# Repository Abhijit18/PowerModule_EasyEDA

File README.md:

# XIAO ESP32-C3 / 18650 Mini-UPS — Copilot + EasyEDA Pro Engineering Workspace

> **ENGINEERING DEVELOPMENT / NO FABRICATION APPROVAL.** This is a complete Git repository of requirements, source design artifacts, engineering evidence, scripts, firmware test harness, and AI assistant instructions. It is **not** a finished or verified Rev C PCB. The original Gerber package and Rev B PCB are evidence / draft baselines, not certified source of truth for electrical equivalence.

## Mission
Rework the supplied power-switching board into an affordable, hand-assemblable EasyEDA Pro design. A single *protected 18650 3.7 V nominal* cell and the existing XIAO ESP32-C3 onboard USB charger/power circuitry should keep a **verified-compatible 3.3 V microphone** and ESP32 alive through 5 V input failures, while a **D1/GPIO3-driven transistor** controls a relay. Preserve D2–D10 GPIO breakouts and relay NO/COM/NC; document any original-function differences. Prefer through-hole carrier components; the preassembled XIAO is necessarily SMT internally.

## What is included

| Folder / file | Purpose |
|---|---|
| `reference/original/` | User's original schematic PNG and Gerber ZIP; immutable historical input |
| `reference/rev-b/` | Rev B EasyEDA Standard JSON, KiCad draft, native previews and supplier BOM, **unvalidated** |
| `hardware/rev-c/` | Revision C target design contract, net map, component target, holder fit checks |
| `docs/` | Electrical architecture, source traceability, decisions, BOM, risks, validation and fabrication gates |
| `.github/copilot-instructions.md` / `AGENTS.md` | Always-on AI guardrails and navigation |
| `.github/agents/` | Specialist electrical, EasyEDA, reviewer, sourcing and test agents |
| `.github/skills/` | Reusable MCP, power-path, schematic, PCB, BOM and bring-up playbooks |
| `.github/prompts/` | Ready-to-run Copilot slash prompts by engineering phase |
| `.vscode/mcp.json` | Project-local MCP server with **read-only** starting profile |
| `firmware/` | Non-production heartbeat/relay verification sketch |
| `scripts/` and `tests/` | Executable requirements and file integrity checks |
| `evidence/` | Templates for per-revision engineering review evidence |

## Getting started (Windows / VS Code / EasyEDA Pro)

1. Extract this repository, open its **root folder** in VS Code, and enable GitHub Copilot Chat.
2. Install **Node.js 24.x** and EasyEDA Pro. Read [`docs/mcp-setup.md`](docs/mcp-setup.md). The `npx` MCP install needs internet access and the EasyEDA extension must be imported in the Pro UI.
3. Run `npx easyeda-mcp-pro extension --open`; import `easyeda-bridge-extension.eext` in **Advanced → Extensions Manager**, allow external interaction, restart EasyEDA Pro, and use **MCP Bridge → Connect Local**.
4. In VS Code start the `easyeda-mcp-pro` MCP server using `.vscode/mcp.json`; open a disposable EasyEDA Pro project or import the Rev B Standard JSON as an **unverified baseline**. Run `npx easyeda-mcp-pro --doctor` if offline.
5. In Copilot Chat choose **circuit-architect** agent and run `/audit-original-circuit`, then `/design-rev-c-schematic` with existing project focused in EasyEDA Pro.
6. Only after reviewing the proposed changes, switch MCP to a suitable **write-capable tool profile** and grant explicit, scoped approval for changes (`confirmWrite=true` where required). **Do not enable unsupervised writes or generate manufacturing files as the first action.**
7. Run `python scripts/validate_repo.py` and `python -m unittest discover -s tests -v` locally. CI checks reference integrity, documented requirements and evidence file references, **not** electrical functionality. Executed tests and PASS gates require actual evidence paths rather than blanket NOT_RUN status.

### First Copilot request

> Read `AGENTS.md`, `docs/requirements.md`, `docs/architecture.md`, `docs/source-traceability.md`, and `hardware/rev-c/design-contract.json`. First call EasyEDA MCP read-only tools to inspect the focused project (list components, nets, XIAO pin map, battery/relay connections, project identity). Produce a pin-by-pin discrepancy matrix vs the original schematic and Rev B draft, distinguishing verified facts from assumptions. Do not write to EasyEDA or change the 5 V power circuitry yet. Propose a Rev C schematic plan and missing evidence.

## Engineering status

- **Original**: Schematic and Gerbers supplied by owner; original board may have external 5 V boost, charge-status and power-switch semantics that Rev B changed.
- **Rev B**: Files imported as draft reference; not independently opened in EasyEDA Pro or checked with its ERC/DRC. Its original design docs explicitly flag several non-equivalent interfaces.
- **Rev C**: Target requirements and process packaged here. **No native EasyEDA Pro Rev C schematic, routed PCB, tested 18650 footprint or Gerbers are claimed**.
- **Hard release blockers**: microphone nominal voltage/current unknown; exact 18650 cell/holder dimensions unknown; state of charger and external-5V path not verified on actual XIAO revision; combined 3.3 V peak current not measured; source-to-target functional equivalence incomplete.

### Push to GitHub (after extracting)

This ZIP contains a local Git repository with an initial commit. No GitHub remote is automatically created.

```powershell
# In a PowerShell terminal inside the extracted folder:
git status
# Create a new *private* repository on GitHub using the web UI, then:
git remote add origin https://github.com/YOUR-USER/xiao-esp32c3-ups-copilot.git
git push -u origin main
```

If `gh` is installed and authenticated, an alternative is `gh repo create xiao-esp32c3-ups-copilot --private --source . --remote origin --push`. Review all reference files before publishing; the original design is included.

## Essential boundaries

Never connect 230 V AC directly to the 5 V terminal. Never put an unprotected lithium cell into a charger circuit without verifying its safety requirements. Never infer a manufacturing-safe PCB from a pretty 3D concept or autorouter's zero-unconnected result. Keep the original and Rev B references read-only and do all edits under `hardware/rev-c/` / an explicitly named EasyEDA Pro project. See `docs/safety-gates.md`.

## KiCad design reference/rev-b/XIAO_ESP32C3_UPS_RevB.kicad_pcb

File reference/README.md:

# Immutable source evidence

`original/` is the owner's uploaded schematic and Gerber ZIP. `rev-b/` are assistant-produced draft EasyEDA Standard and KiCad artifacts **not independently verified inside EasyEDA Pro**. These are historical references, not engineering release files; do not alter their contents. New editable designs belong in `hardware/rev-c/` and in a separate owner-approved EasyEDA Pro project. Source files can contain errors and require datasheet + native net/readback validation. These files may be proprietary; review sharing before pushing to a public repository.

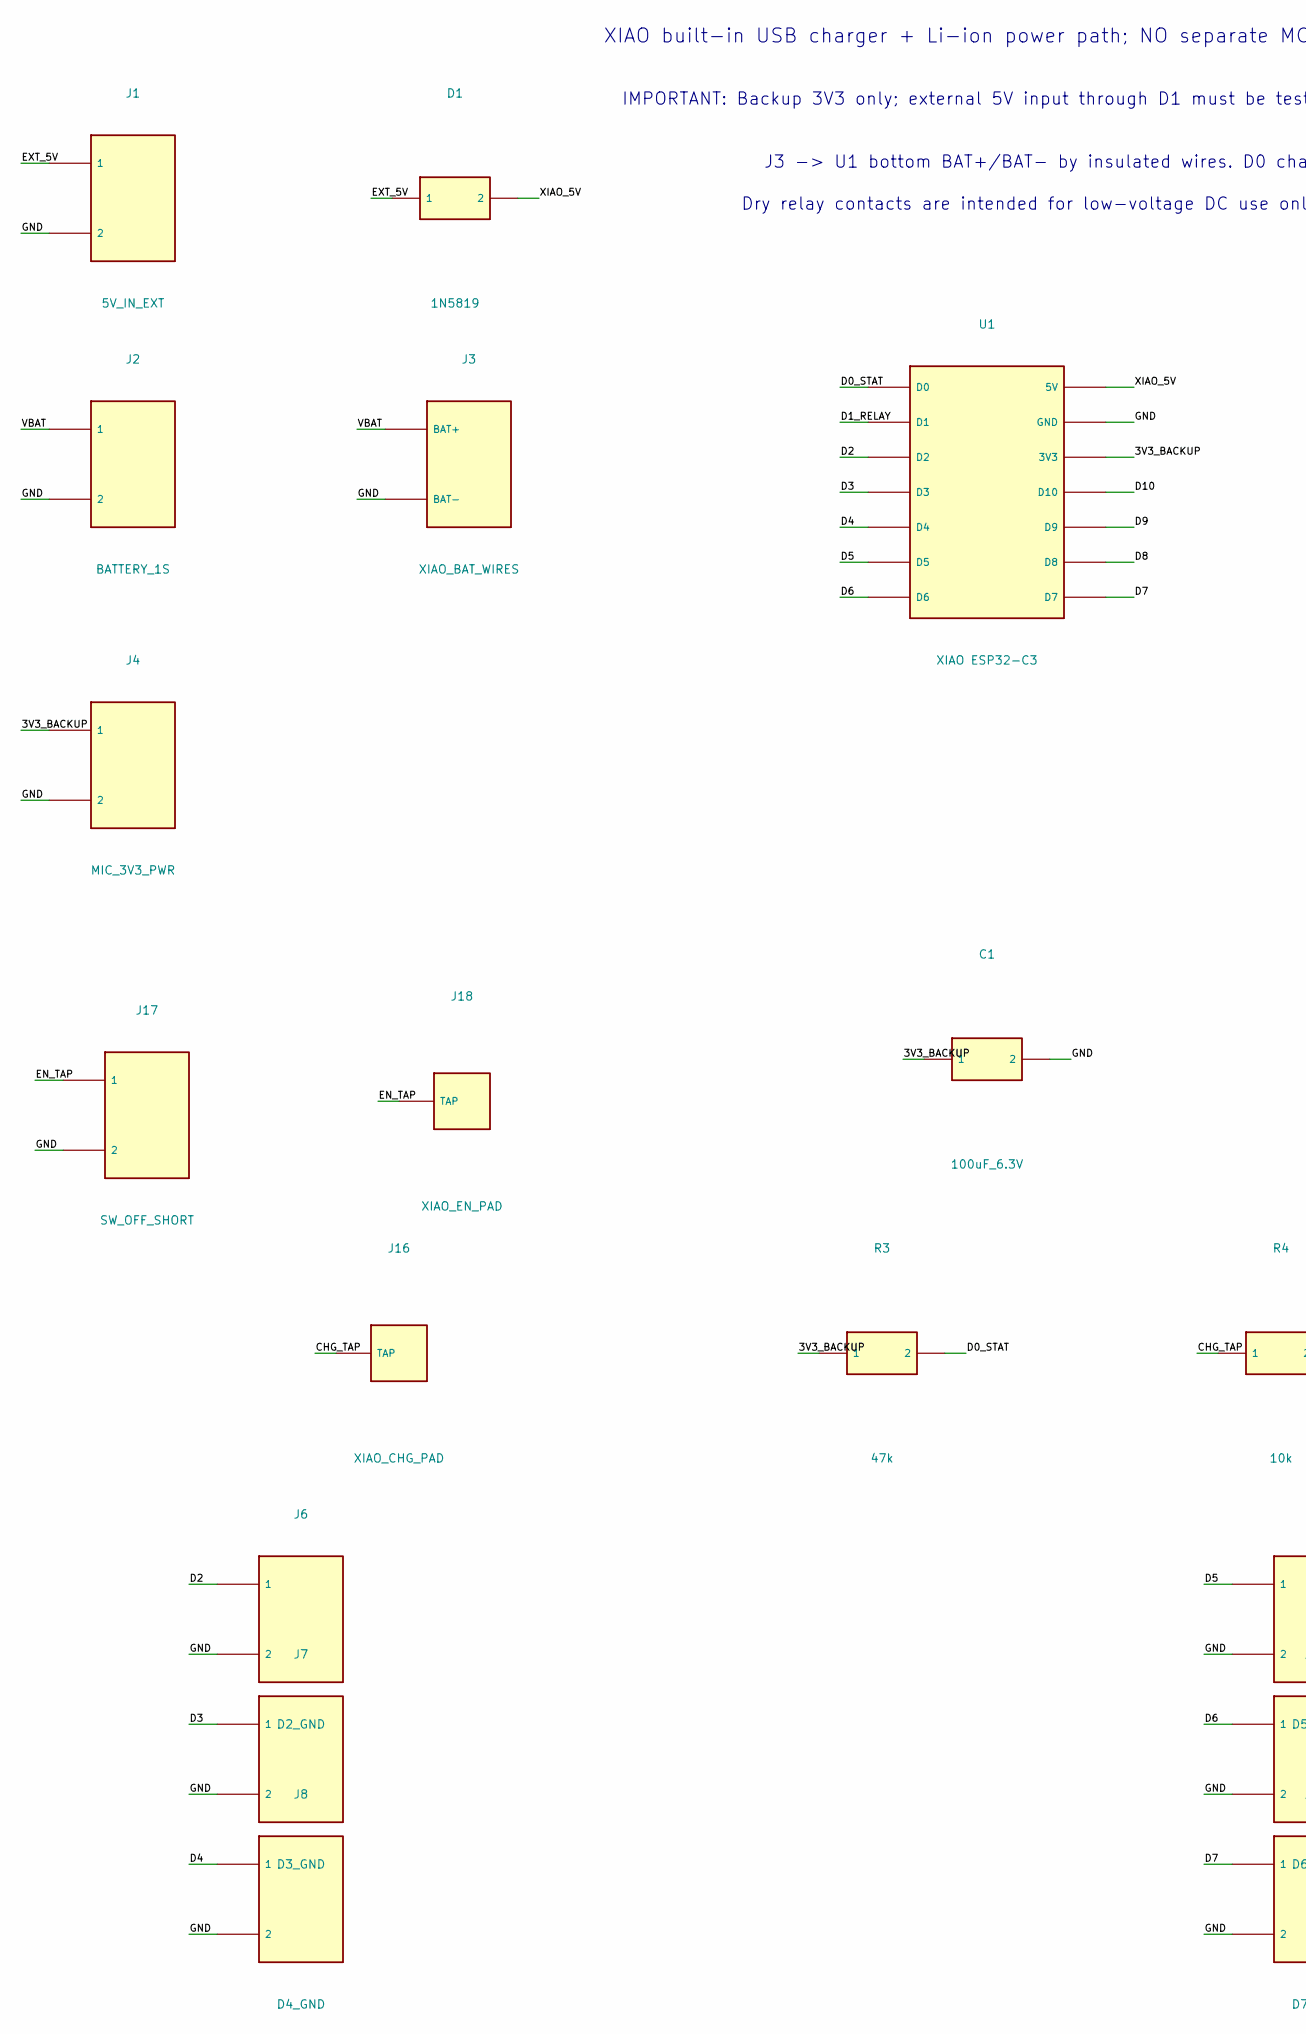
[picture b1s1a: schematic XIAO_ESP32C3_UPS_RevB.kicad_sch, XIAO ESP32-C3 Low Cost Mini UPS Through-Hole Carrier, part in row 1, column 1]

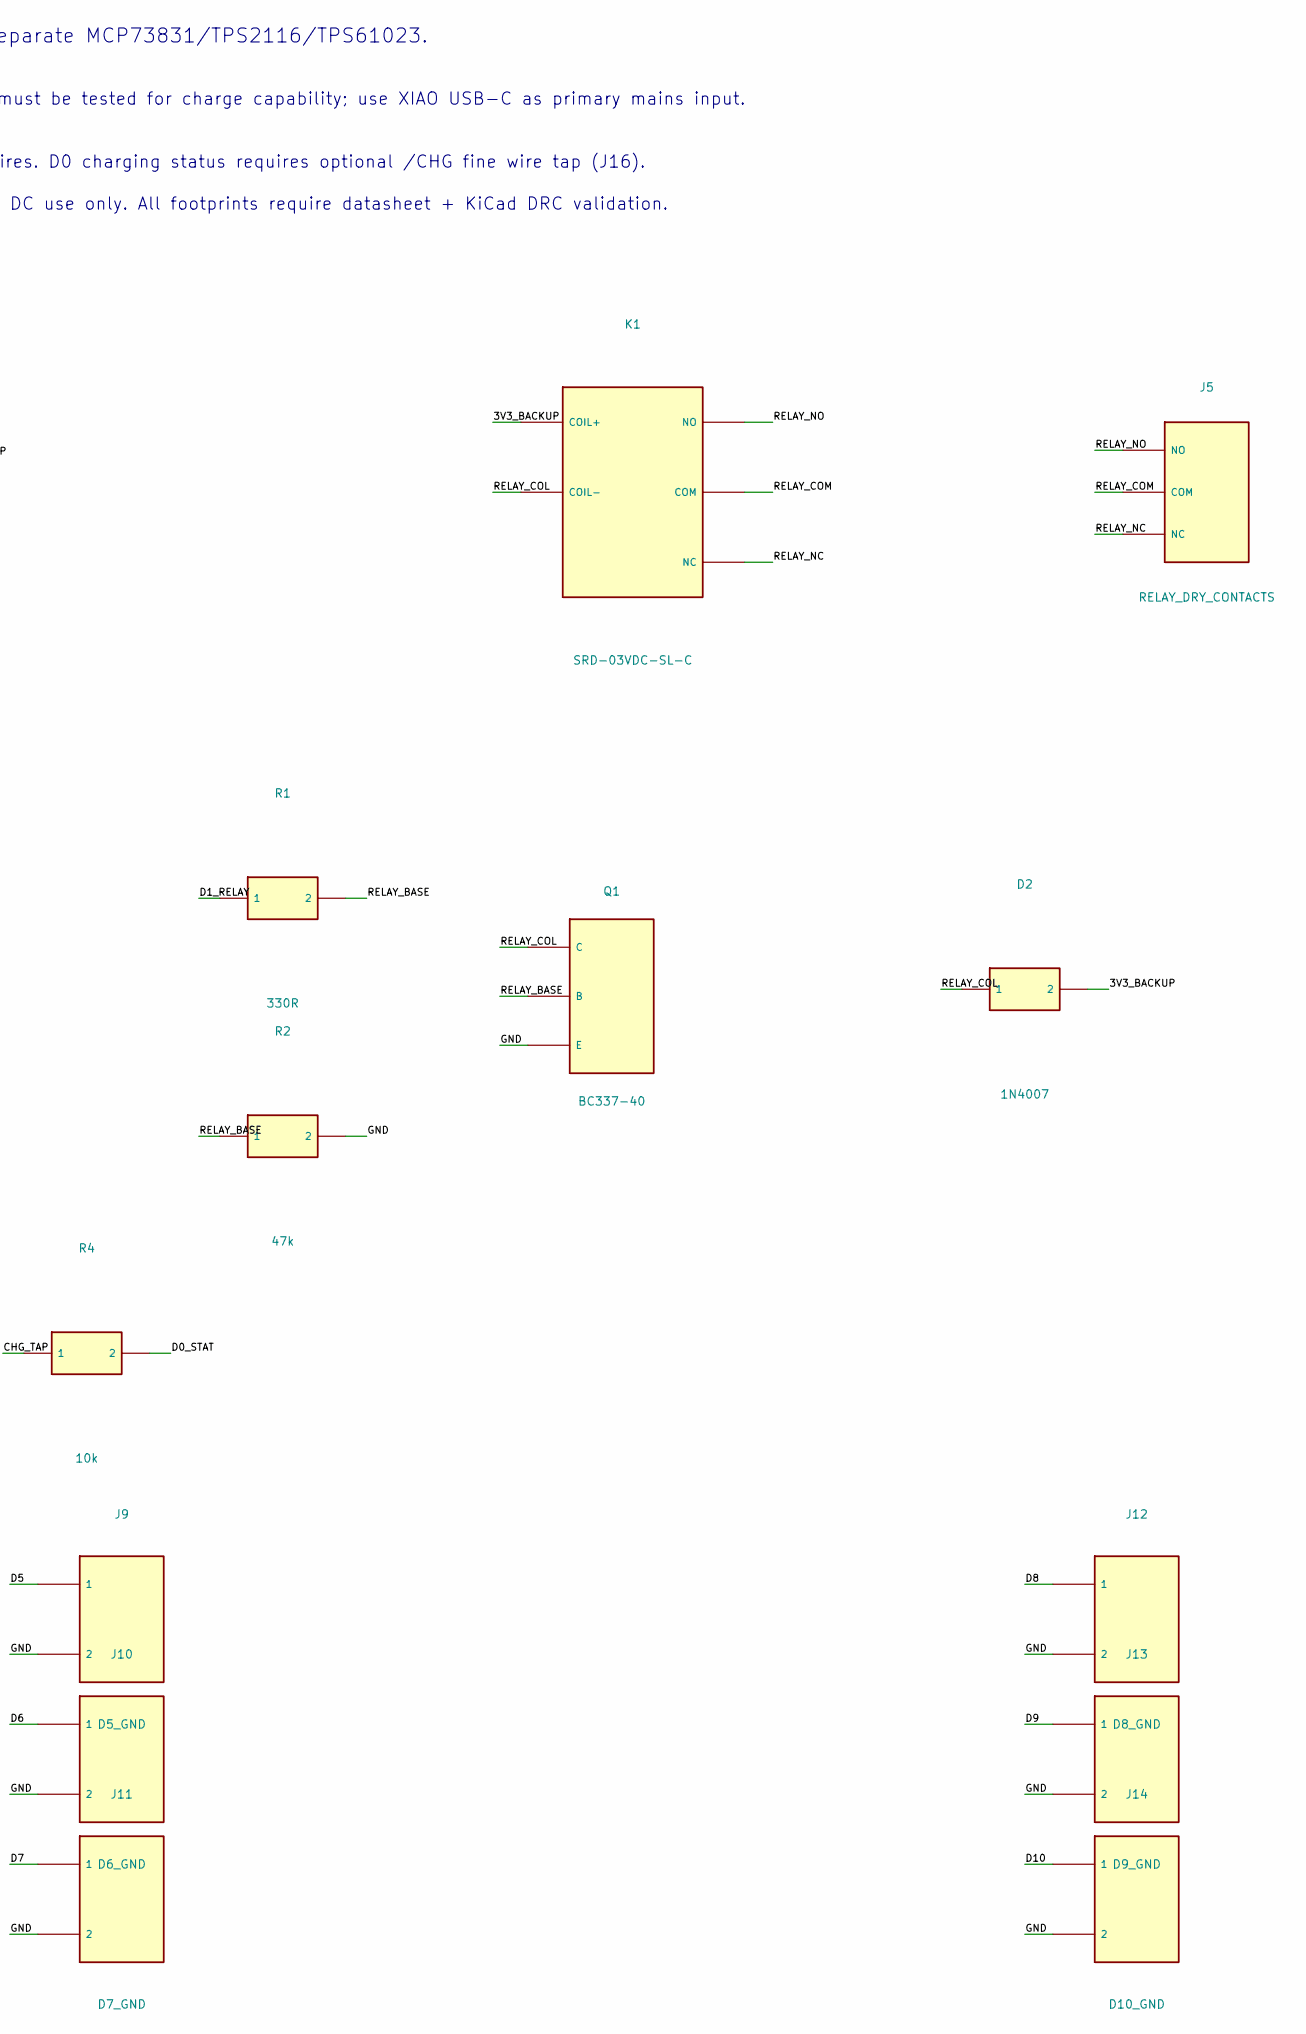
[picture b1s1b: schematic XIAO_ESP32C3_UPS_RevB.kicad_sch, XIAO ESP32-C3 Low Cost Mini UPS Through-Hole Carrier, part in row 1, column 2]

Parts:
C1: 100uF_6.3V; C_RADIAL
D1: 1N5819; D_AXIAL
D2: 1N4007; D_AXIAL
J1: 5V_IN_EXT; TERMINAL2
J2: BATTERY_1S; TERMINAL2
J3: XIAO_BAT_WIRES; WIRE2
J4: MIC_3V3_PWR; TERMINAL2
J5: RELAY_DRY_CONTACTS; TERMINAL3
J6: D2_GND; HEADER2
J7: D3_GND; HEADER2
J8: D4_GND; HEADER2
J9: D5_GND; HEADER2
J10: D6_GND; HEADER2
J11: D7_GND; HEADER2
J12: D8_GND; HEADER2
J13: D9_GND; HEADER2
J14: D10_GND; HEADER2
J16: XIAO_CHG_PAD; TESTPAD
J17: SW_OFF_SHORT; TERMINAL2
J18: XIAO_EN_PAD; TESTPAD
K1: SRD-03VDC-SL-C; SRD3
Q1: BC337-40; TO92
R1: 330R; R_AXIAL
R2, R3: 47k; R_AXIAL
R4: 10k; R_AXIAL
U1: XIAO ESP32-C3; XIAO

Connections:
3V3_BACKUP: C1.1, D2.2, J4.1, K1.1 (COIL+), R3.1, U1.12 (3V3)
CHG_TAP: J16.1, R4.1
D0_STAT: R3.2, R4.2, U1.1 (D0)
D1_RELAY: R1.1, U1.2 (D1)
D2: J6.1, U1.3 (D2)
D3: J7.1, U1.4 (D3)
D4: J8.1, U1.5 (D4)
D5: J9.1, U1.6 (D5)
D6: J10.1, U1.7 (D6)
D7: J11.1, U1.8 (D7)
D8: J12.1, U1.9 (D8)
D9: J13.1, U1.10 (D9)
D10: J14.1, U1.11 (D10)
EN_TAP: J17.1, J18.1
EXT_5V: D1.1, J1.1
GND: C1.2, J1.2, J2.2, J3.2 (BAT-), J4.2, J6.2, J7.2, J8.2, J9.2, J10.2, J11.2, J12.2, J13.2, J14.2, J17.2, Q1.3 (E), R2.2, U1.13 (GND)
RELAY_BASE: Q1.2 (B), R1.2, R2.1
RELAY_COL: D2.1, K1.2 (COIL-), Q1.1 (C)
RELAY_COM: J5.2 (COM), K1.4 (COM)
RELAY_NC: J5.3 (NC), K1.5 (NC)
RELAY_NO: J5.1 (NO), K1.3 (NO)
VBAT: J2.1, J3.1 (BAT+)
XIAO_5V: D1.2, U1.14 (5V)

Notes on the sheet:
XIAO built-in USB charger + Li-ion power path; NO separate MCP73831/TPS2116/TPS61023.
IMPORTANT: Backup 3V3 only; external 5V input through D1 must be tested for charge capability; use XIAO USB-C as primary mains input.
J3 -> U1 bottom BAT+/BAT- by insulated wires. D0 charging status requires optional /CHG fine wire tap (J16).
Dry relay contacts are intended for low-voltage DC use only. All footprints require datasheet + KiCad DRC validation.

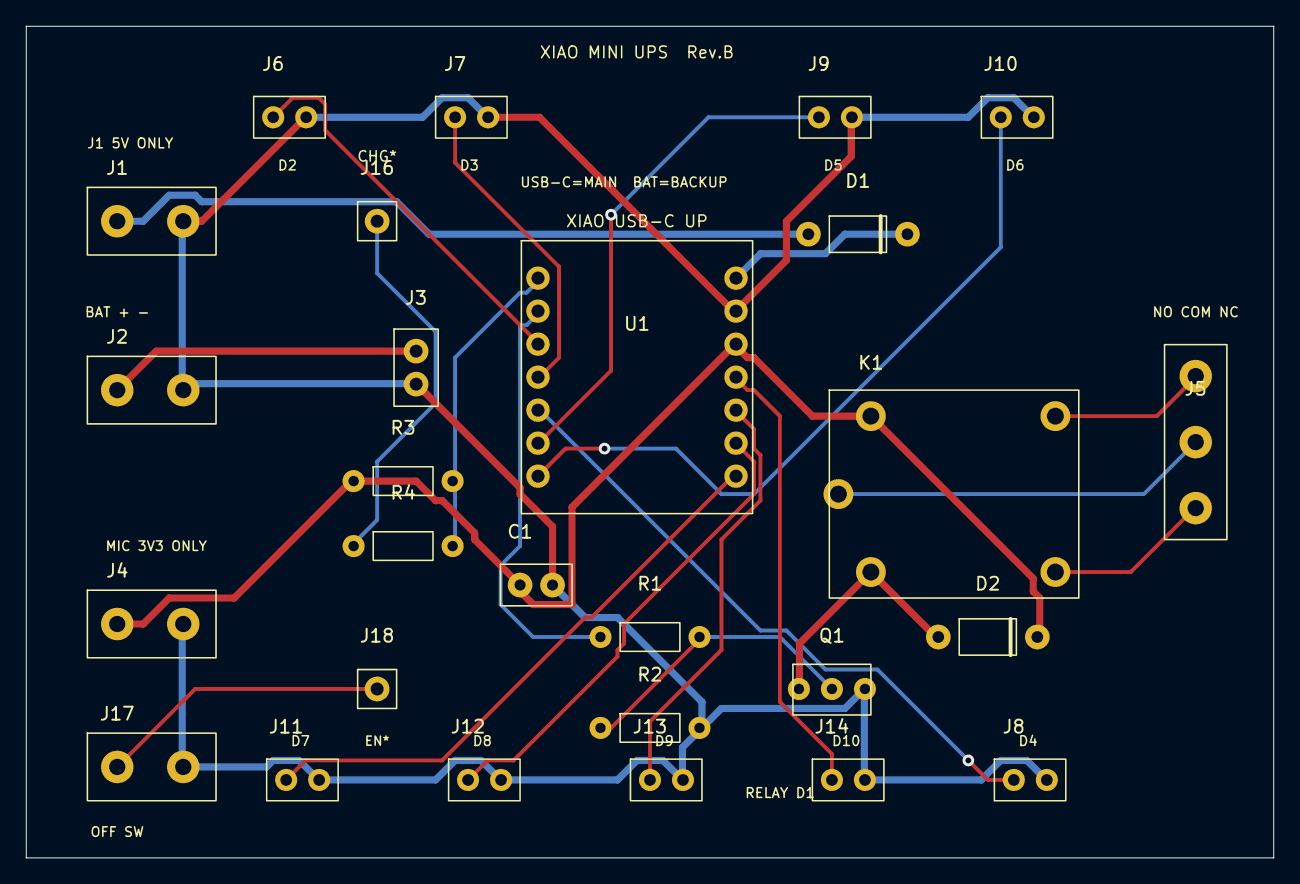
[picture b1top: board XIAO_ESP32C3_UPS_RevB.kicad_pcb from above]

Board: 2 copper layers, 96.0 x 64.0 mm, 27 parts (0 on the bottom side), 23 nets.

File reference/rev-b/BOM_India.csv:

Reference,Part,Qty,Type,India_sourcing_search,Critical_note
U1,Seeed XIAO ESP32C3,1,preassembled module THT carrier,https://robu.in/?s=xiao+esp32c3&post_type=product,Integrated lithium charger ~380mA
K1,SRD-03VDC-SL-C 3V SPDT relay,1,THT,https://evelta.com/srd-3v-15a-1formc-high-power-relay-throug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,Must verify footprint and 3.3V maximum coil rating
Q1,BC337-40 transistor TO-92,1,THT,https://robu.in/?s=BC337&post_type=product,Pinout check C-B-E
D1,1N5819 1A Schottky,1,THT,https://robu.in/?s=1N5819&post_type=product,Alternative screw-terminal 5V input protection
D2,1N4007 flyback,1,THT,https://robu.in/?s=1N4007&post_type=product,Cathode to backed 3V3
R1,330 ohm 0.25W,1,THT,https://robu.in/?s=330+ohm+resistor&post_type=product,BC337 base
R2-R3,47k 0.25W,2,THT,https://robu.in/?s=47k+resistor&post_type=product,Pulldown and charge status pullup
R4,10k 0.25W,1,THT,https://robu.in/?s=10k+resistor&post_type=product,Optional charge status series
C1,100uF >=6.3V radial electrolytic,1,THT,https://robu.in/?s=100uf+electrolytic&post_type=product,Near 3V3 backed relay
J1 J2 J4,2-pin 5.08mm THT terminal block,3,THT,https://robu.in/?s=2+pin+terminal+block+5.08&post_type=product,Battery polarity; insulated 5V adapter only
J5,3-pin 5.08mm THT terminal block,1,THT,https://robu.in/?s=3+pin+terminal+block+5.08&post_type=product,Low voltage relay dry contacts
J6-J14,2-pin 2.54mm THT header,9,THT,https://robu.in/?s=2+pin+header+2.54&post_type=product,GPIO with paired GND
J3,2-pin 2.54mm THT solder wire link,1,THT,https://robu.in/?s=2+pin+header+2.54&post_type=product,Two insulated wires connect to module bottom battery pads
J16,1-pin 2.54mm pad,1,THT,https://robu.in/?s=pin+header&post_type=product,OPTIONAL /CHG pad tap; verify XIAO location
J17,2-pin terminal block switch connector,1,THT,https://robu.in/?s=2+pin+terminal+block+5.08&post_type=product,OPTIONAL: short to hold EN low via J18
J18,1-pin 2.54mm EN tap pad,1,THT,https://robu.in/?s=pin+header&post_type=product,OPTIONAL insulated wire to XIAO EN testpad
